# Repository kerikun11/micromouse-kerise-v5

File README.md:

# MicroMouse KERISE v5

ハーフサイズマイクロマウス

## 戦績

なし

## スペック

| 部品               | 型番          | 備考                              |
| :----------------- | :------------ | :-------------------------------- |
| モーター           | 不明          | 直径6mm 長さ10mm コアレスモーター |
| エンコーダ         | MA730         | 4096パルス 磁気式                 |
| マイコン           | ESP32-PICO-D4 | 240MHz dual core                  |
| 赤外線LED          | SFH4045N      | 波長940mm                         |
| フォトトランジスタ | SFH3015FA     | 波長940nm                         |
| モータードライバ   | DRV8835       | 最大電流1.5A x 2ch                |
| 6軸センサ          | ICM-20602     | 3軸ジャイロ+3軸加速度             |
| バッテリー         | 不明          | 3.7V 25C 100mAh 1S                |

## 回路設計

- KiCad

## 機体設計

- Fusion 360

## 開発環境

- PlatformIO Espressif32 Arduino

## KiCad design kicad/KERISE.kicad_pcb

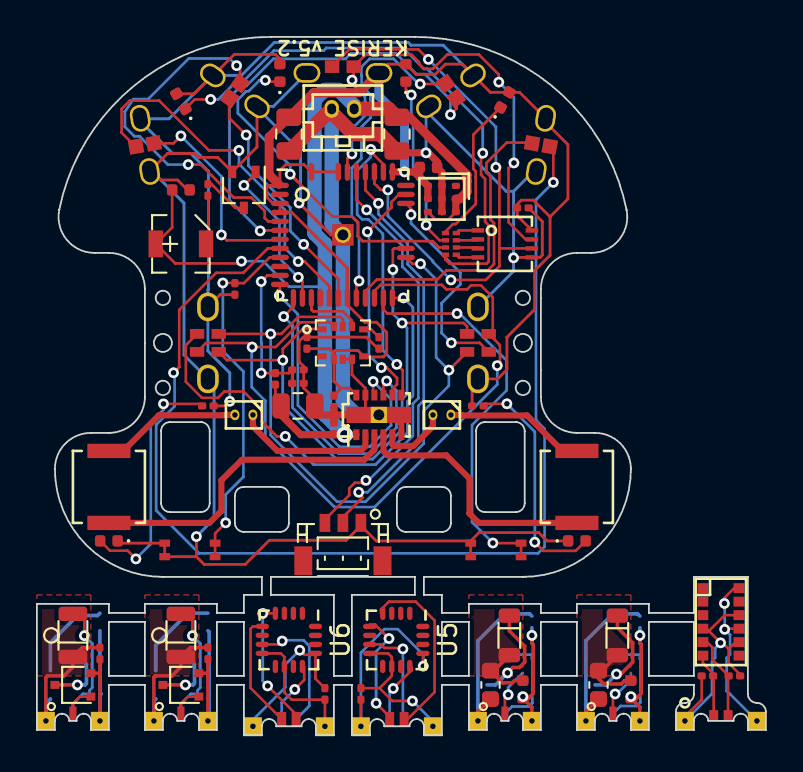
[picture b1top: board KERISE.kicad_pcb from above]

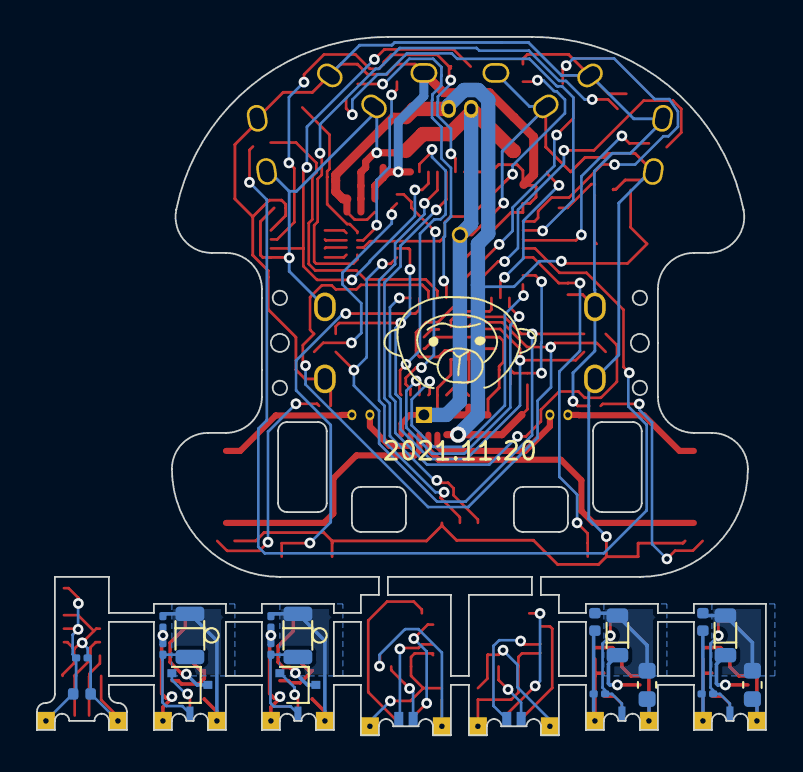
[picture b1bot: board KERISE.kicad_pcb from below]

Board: 2 copper layers, 40.5 x 38.8 mm, 90 parts (18 on the bottom side), 88 nets.

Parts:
BT1: Battery; Hirose_DF13-02P-1.25DSA_02x1.25mm_Straight
C1, C5: 10u; C_0402_1005Metric
C2: 4.7u; C_0402_1005Metric
C3, C4, C6, C7, C9, C11, C12, C13, C15, C17, C18, C22, C23: 0.1u; C_0201_0603Metric
C8, C10, C14, C16: 1u; C_0402_1005Metric
C19, C20, C21: 47u; C_0805_2012Metric
D1, D2, D3, D4: LED; LED_0402_1005Metric
D5, D6, D7, D8: SFH4045N; SFH4045N_L
D9, D10: Power; LED_0402_1005Metric
J1, J3, J10, J12: Host; IR_HOST_V_04
J2, J4, J11, J13: Slave; IR_SLAVE_V_04
J5, J7: ENC_Host; STAND_HOST_06
J6, J8: ENC_Slave; STAND_SLAVE_06
J9: COM; JST_SH_BM03B-SRSS-TB_03x1.00mm_Straight
J14: Motor_L; SMD_conn_2
J15: Motor_R; SMD_conn_2
L1, L2: 47u; L_4018
LS1: Speaker; SMT-0340-T-R
P1: ToF_Host; STAND_HOST_04
P2: ToF_Slave; STAND_SLAVE_04
Q1, Q2, Q4, Q6, Q8: DMN3065LW-7; SOT-323_SC-70
Q3, Q5, Q7, Q9: SFH3015FA; SFH3015FA_L
R1, R6, R8, R10, R12, R13, R14: 10k; R_0201_0603Metric
R2, R3: 4.7k; R_0201_0603Metric
R4: 10; R_0201_0603Metric
R5, R7, R9, R11: 100; R_0603_1608Metric
R15, R16: 1k; R_0201_0603Metric
RN1: EXB-18V102JX; R_Array_Concave_4x0201
SW1: RESET; EVPBB
SW2: UPLOAD; EVPBB
U1: ESP32-PICO-D4
U2: VL6180X
U3: PCA9632; DFN-8-1EP_3x3mm_Pitch0.5mm
U4: ICM-20600
U5, U6: MA730
U7: LXDC2UR30; LXDC2UR
U8: DRV8835

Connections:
+3V3: C1.2, C4.1, C6.1, C20.1, C23.1, D1.2, D2.2, D3.2, D4.2, J1.1, J3.1, J5.1, J7.1, J10.1, J12.1, P1.1, R1.2, R15.1, R16.1, U1.1, U1.3, U1.4, U1.19, U1.37, U1.43, U1.46, U3.8, U4.5, U4.8, U7.3, U7.4, U8.12
+BATT: BT1.1, C5.1, C19.1, C21.1, C22.1, LS1.1, R13.1, U7.5, U7.7, U7.8, U8.1
/Encoder_L/s_CS: J6.2, U5.5
/Encoder_L/s_GND: C12.2, J6.6, U5.8, U5.10
/Encoder_L/s_MISO: J6.5, U5.7
/Encoder_L/s_MOSI: J6.4, U5.4
/Encoder_L/s_SCLK: J6.3, U5.12
/Encoder_L/s_VDD: C12.1, J6.1, U5.13
/Encoder_R/s_CS: J8.2, U6.5
/Encoder_R/s_GND: C13.2, J8.6, U6.8, U6.10
/Encoder_R/s_MISO: J8.5, U6.7
/Encoder_R/s_MOSI: J8.4, U6.4
/Encoder_R/s_SCLK: J8.3, U6.12
/Encoder_R/s_VDD: C13.1, J8.1, U6.13
/IR_RCV_FL/LED_to_C: C10.1, D6.2, R7.2
/IR_RCV_FL/LED_to_FET: D6.1, Q4.3
/IR_RCV_FL/s_3.3V: C11.1, J4.1, Q5.1, R7.1
/IR_RCV_FL/s_GND: C10.2, C11.2, J4.4, Q4.2, R8.2
/IR_RCV_FL/s_IR_LED: J4.2, Q4.1
/IR_RCV_FL/s_IR_RCV: J4.3, Q5.2, R8.1
/IR_RCV_FR/LED_to_C: C8.1, D5.2, R5.2
/IR_RCV_FR/LED_to_FET: D5.1, Q2.3
/IR_RCV_FR/s_3.3V: C9.1, J2.1, Q3.1, R5.1
/IR_RCV_FR/s_GND: C8.2, C9.2, J2.4, Q2.2, R6.2
/IR_RCV_FR/s_IR_LED: J2.2, Q2.1
/IR_RCV_FR/s_IR_RCV: J2.3, Q3.2, R6.1
/IR_RCV_SL/LED_to_C: C16.1, D8.2, R11.2
/IR_RCV_SL/LED_to_FET: D8.1, Q8.3
/IR_RCV_SL/s_3.3V: C17.1, J13.1, Q9.1, R11.1
/IR_RCV_SL/s_GND: C16.2, C17.2, J13.4, Q8.2, R12.2
/IR_RCV_SL/s_IR_LED: J13.2, Q8.1
/IR_RCV_SL/s_IR_RCV: J13.3, Q9.2, R12.1
/IR_RCV_SR/LED_to_C: C14.1, D7.2, R9.2
/IR_RCV_SR/LED_to_FET: D7.1, Q6.3
/IR_RCV_SR/s_3.3V: C15.1, J11.1, Q7.1, R9.1
/IR_RCV_SR/s_GND: C14.2, C15.2, J11.4, Q6.2, R10.2
/IR_RCV_SR/s_IR_LED: J11.2, Q6.1
/IR_RCV_SR/s_IR_RCV: J11.3, Q7.2, R10.1
/Motor/MT_OUT_L1: J14.1, U8.2
/Motor/MT_OUT_L2: J14.2, L1.1
/Motor/MT_OUT_L_L: L1.2, U8.3
/Motor/MT_OUT_L_R: L2.2, U8.4
/Motor/MT_OUT_R1: J15.1, L2.1
/Motor/MT_OUT_R2: J15.2, U8.5
/ToF/s_3.3V: C2.1, C3.1, P2.1, R2.1, R3.1, U2.4, U2.8, U2.10
/ToF/s_GND: C2.2, C3.2, P2.4, U2.9, U2.12
/ToF/s_SCL: P2.3, R3.2, U2.5
/ToF/s_SDA: P2.2, R2.2, U2.6
BAT-VOL: C18.1, R13.2, R14.1, U1.11
BUTTON: SW2.1, U1.23
GND: BT1.2, C1.1, C4.2, C5.2, C6.2, C7.2, C18.2, C19.2, C20.2, C21.2, C22.2, C23.2, D9.1, D10.1, J1.4, J3.4, J5.6, J7.6, J9.1, J10.4, J12.4, P1.4, Q1.2, R14.2, SW1.2, SW2.2, U1.49, U3.5, U4.6, U4.7, U7.2, U7.6, U7.9, U8.6, U8.11, U8.13
I2C-SCL: P1.3, U1.39, U3.6
I2C-SDA: P1.2, U1.42, U3.7
MT-IN-L1: U1.12, U8.10
MT-IN-L2: U1.13, U8.9
MT-IN-R1: U1.35, U8.8
MT-IN-R2: U1.38, U8.7
unnamed: C7.1, U4.11
unnamed: D1.1, RN1.5
unnamed: D2.1, RN1.6
unnamed: D3.1, RN1.7
unnamed: D4.1, RN1.8
unnamed: D9.2, R15.2
unnamed: D10.2, R16.2
unnamed: LS1.2, R4.1
unnamed: Q1.3, R4.2
unnamed: R1.1, SW1.1, U1.9
unnamed: RN1.1, U3.4
unnamed: RN1.2, U3.3
unnamed: RN1.3, U3.2
unnamed: RN1.4, U3.1
PR-LED-FL: J3.2, U1.17
PR-LED-FR: J1.2, U1.21
PR-LED-SL: J12.2, U1.18
PR-LED-SR: J10.2, U1.20
PR-RCV-FL: J3.3, U1.7
PR-RCV-FR: J1.3, U1.8
PR-RCV-SL: J12.3, U1.5
PR-RCV-SR: J10.3, U1.6
SPEAKER: Q1.1, U1.14
SPI-CS-ENC_L: J5.2, U1.24
SPI-CS-ENC_R: J7.2, U1.34
SPI-CS-IMU: U1.15, U4.12
SPI-MISO: J5.5, J7.5, U1.29, U4.1
SPI-MOSI: J5.4, J7.4, U1.22, U4.14
SPI-SCLK: J5.3, J7.3, U1.28, U4.13
UART-RX: J9.2, U1.40
UART-TX: J9.3, U1.41

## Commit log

2017-12-04 KiCad設計中のファイルを追加
    ESP32-PICO-D4版
2017-12-06 自動配線成功
2017-12-06 バッテリーコネクタの位置を改良
    電池に干渉しないように．
    自動配線成功済
2017-12-10 基板発注
    KERISEv5初版はこのデータで発注済
2018-01-04 回路を改良
    受光部をフォトトランジスタに変更
    測距センサをVL6180Xに変更
    動作電圧を3Vに変更
2018-01-05 電源ラインを配線
    あとは自動配線
2018-01-08 7本残して自動配線終了
2018-01-08 電源回りの配線を改良
2018-01-08 自動配線を適用，LOGOを貼り付け
2018-04-09 部品を配置
2018-04-30 自動配線を適用
2018-05-13 回路図を改良
2020-05-10 回路にMA702を追加
2020-05-10 回路を編集 ToFを除去
2020-05-10 エンコーダ基板を調整，配線可能に
2020-05-10 自動配線4本Take2
2020-05-10 KERISEv5に向けて回路図を更新
2020-05-10 手動配線
2020-05-10 配線を修正
    - エンコーダの配線が基板外に出てた（Elecrowから指摘）
2020-05-10 回路図のPDFを追加
2020-05-10 コンデンサを追加
2020-05-10 自動配線あと4本
2020-05-10 部品を配置 kicad5
2020-05-10 回路図の警告を除去
2020-05-10 未配線あり
2020-05-10 自動配線を適用，基板発注
2020-05-10 フットプリントを改良
2020-05-10 デザインルールを緩和
2020-05-10 配線を改良
2020-05-10 matlabディレクトリを整理
2020-05-10 アンテナを外側に配置
2020-05-10 配置を改良
2020-05-10 LEDの抵抗を集合抵抗に変更
2020-05-10 3Dシェイプを割り当て
2020-05-10 kicad に .gitignore を導入
2020-05-10 自動配線結果
2020-05-10 フットプリントを割り当て
2020-05-10 リファレンスを除去
2020-05-10 以前成功した自動配線を適用，基板発注
2020-05-10 自動配線完了
2020-05-10 エンコーダー基板の位置を調整
2020-05-10 fix pcb margin
2020-05-10 add fusion360 design
2020-05-10 回路を修正，未配線
2020-05-10 予備配線完了
2020-05-10 配線幅を改良
2021-11-19 fix spec
2021-11-20 KiCad: update pcb
2021-12-27 generate sketch PDF
2023-07-08 update to kicad 7
